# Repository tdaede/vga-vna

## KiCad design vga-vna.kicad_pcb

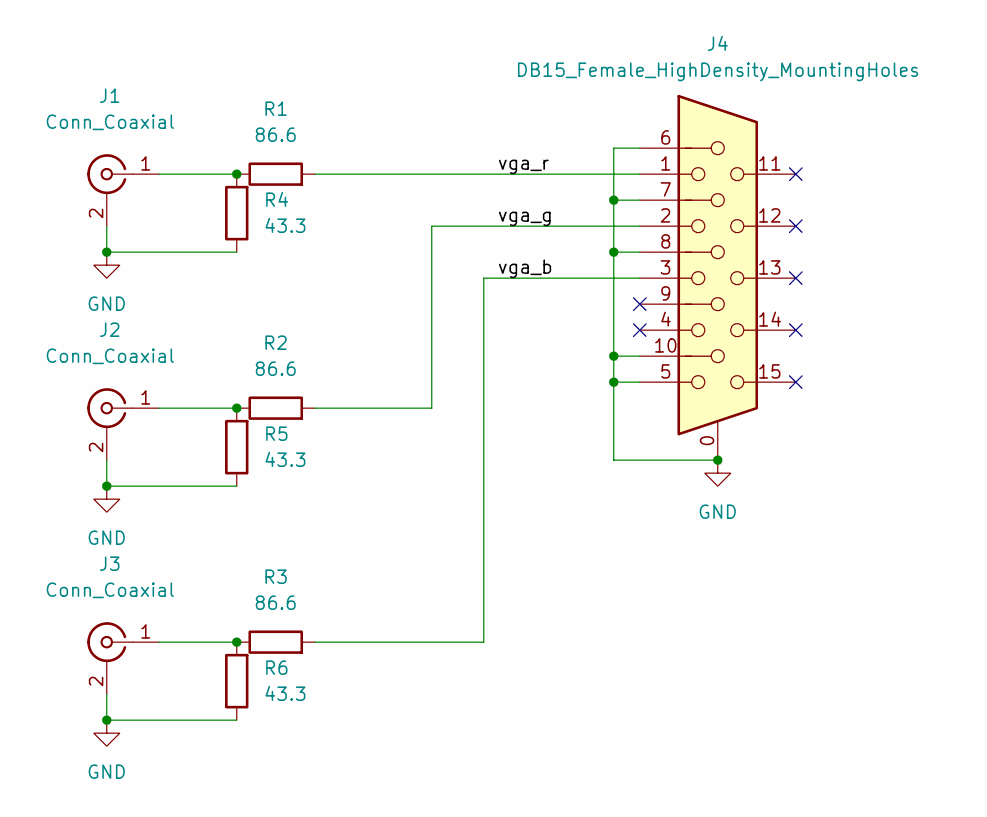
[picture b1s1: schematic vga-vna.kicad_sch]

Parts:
J1, J2, J3: Conn_Coaxial; SMA_Amphenol_901-143_Horizontal; Digikey WM26450-ND
J4: DB15_Female_HighDensity_MountingHoles; DSUB-15-HD_Female_Horizontal_P2.29x1.98mm_EdgePinOffset8.35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; Digikey L77HDE15SD1CH4FVGA-ND
R1, R2, R3: 86.6; R_0805_2012Metric_Pad1.20x1.40mm_HandSolder; Digikey 311-86.6CRCT-ND
R4, R5, R6: 43.3; R_0805_2012Metric_Pad1.20x1.40mm_HandSolder; Digikey 311-43.2CRCT-ND

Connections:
/vga_b: J4.3, R3.2
/vga_g: J4.2, R2.2
/vga_r: J4.1, R1.2
GND: J1.2 (Ext), J2.2 (Ext), J3.2 (Ext), J4.0, J4.5, J4.6, J4.7, J4.8, J4.10, R4.1, R5.1, R6.1
unnamed: J1.1 (In), R1.1, R4.2
unnamed: J2.1 (In), R2.1, R5.2
unnamed: J3.1 (In), R3.1, R6.2

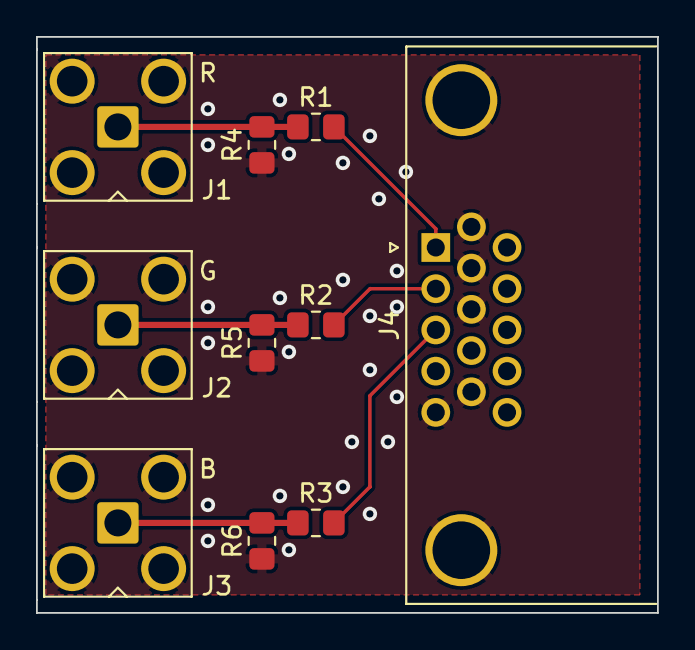
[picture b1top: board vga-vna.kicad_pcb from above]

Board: 2 copper layers, 34.5 x 32.0 mm, 10 parts (0 on the bottom side), 7 nets.

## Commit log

2023-04-26 add license
